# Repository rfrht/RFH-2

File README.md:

# RFH-2
Remote Control unit compatible with most modern Yaesu radios. Includes Schematics, Gerber Files and Board Design.

## What is this?
This is a remote control that is compatible with most modern and recent Yaesu radios. It mimicks the same functionality of [Yaesu FH-2](http://lmgtfy.com/?q=yaesu+fh-2) remote control, at a fraction of the cost ane with a enormous cool factor: YOU CAN ACTUALLY BUILD IT!

Check how [Jim N5JGE](https://www.qrz.com/db/N5JGE) actually built something [**really nifty**](https://github.com/jgedmond/RFH-2/commit/793899766d5572a83a48a860f2a84d2ef02e2b0a) without the need of an enclosure for the board!

## How does the board looks like?
This is the board layout in its full glory (slightly changed from FH-2, because... usability++):

## Did you prototype it?
Yup. Picture below:

## What are the compatible radios?
Yaesu FT-991, FT-991A, FT-950, FTDX-9000, FTDX-5000, FTDX-3000, FT-2000, FTDX-1200, FT-1000MP

## Nice, I liked it! How do I get one?
1. Download the Gerber [.zip file](https://github.com/rfrht/RFH-2/raw/master/Design/RFH-2-gerbers.zip)

2. Send the Gerber ZIP to any PCB Print Service. I have used [JLCPCB](https://jlcpcb.com/quote), they are dead cheap - Paid $2 for 5 boards

3. Buy the switches and the resistors. The most critical part here are the switches: The board has the footprints for this specific switch, which is [Digikey Part EG6117-ND](https://www.digikey.com/products/en?keywords=eg6117-nd). The Resistors and Capacitor are through-hole and the values are in the Schematic.

4. How do I wire it? For wiring, wire the tip of a standard 3-pin audio plug and the `GND` part of the plug. Leave the center floating.

Of course you can also download [Eagle 9](https://www.autodesk.com/products/eagle/free-download) and play with the schematics and PCB layout in [Design](/Design) folder.

## CHANGELOG

### Revision C (May 27, 2024)
* Fixed the flipped Down arrow and F/B button reported in [Issue 1](https://github.com/rfrht/RFH-2/issues/1) by jgedmond - thank you!

### Revision B (Jun 8, 2019)
* Fixed the push-button pinout
* Now makes extensive use of ground plane
* Rewired the board
* Larger holes, suitable for a screw, with symmetrical holes at the board edges
* A through-the-hole pad for the signal input
* Added a few centimeters more to accomodate the $ABOVE changes
* And that's it folks!

### Revision A (Apr 28, 2019)
* Initial release

73s de PY2RAF.

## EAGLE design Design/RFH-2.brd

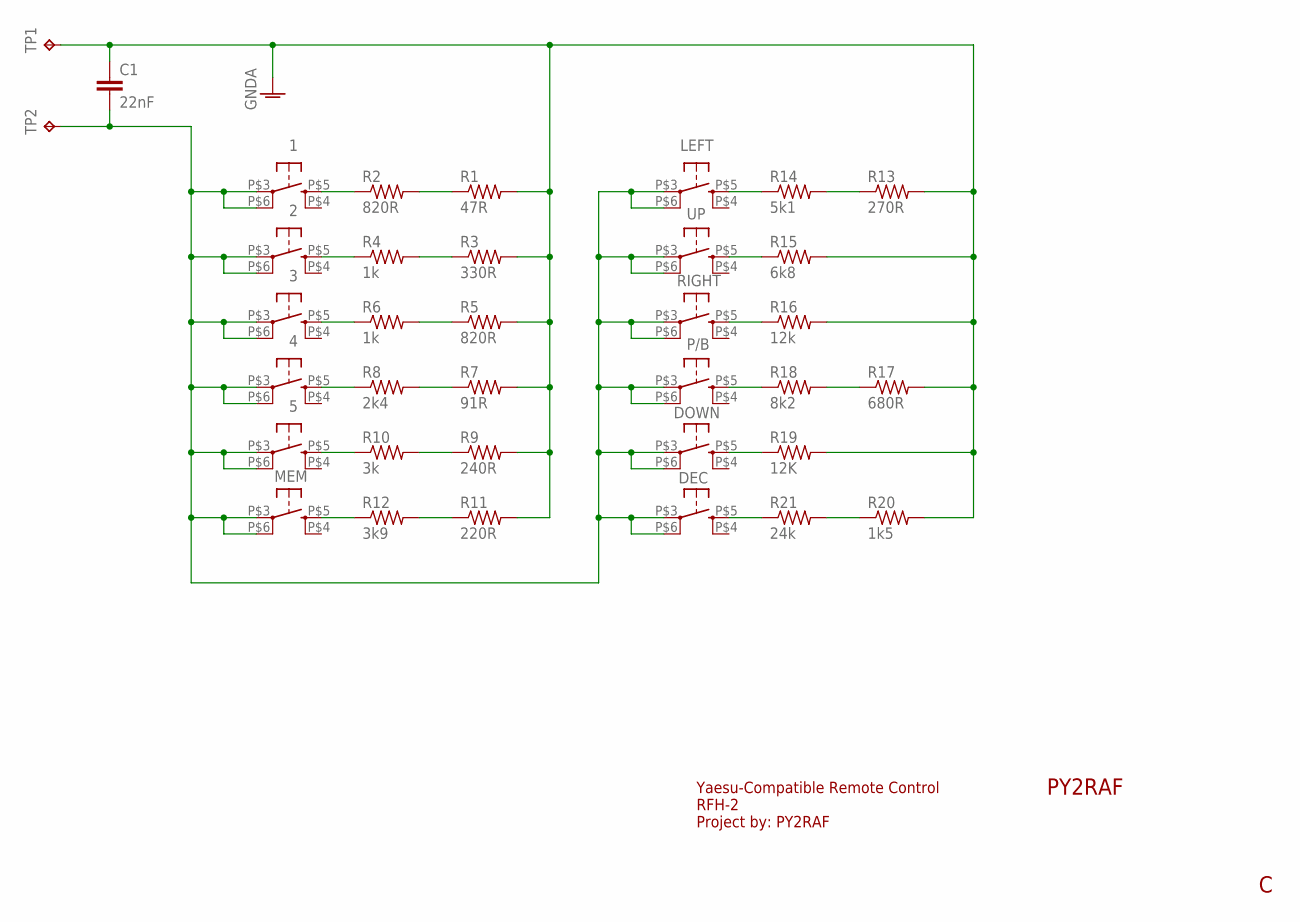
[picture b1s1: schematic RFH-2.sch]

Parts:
1, 2, 3, 4, 5: TL6300-SPST; TL6300
C1: 22nF; C5B3
DEC: TL6300-SPST; TL6300
DOWN: TL6300-SPST; TL6300
LEFT: TL6300-SPST; TL6300
MEM: TL6300-SPST; TL6300
P/B: TL6300-SPST; TL6300
R1: 47R; 0309/10
R2, R5: 820R; 0309/10
R3: 330R; 0309/10
R4, R6: 1k; 0309/10
R7: 91R; 0309/10
R8: 2k4; 0309/10
R9: 240R; 0309/10
R10: 3k; 0309/10
R11: 220R; 0309/10
R12: 3k9; 0309/10
R13: 270R; 0309/10
R14: 5k1; 0309/10
R15: 6k8; 0309/10
R16: 12k; 0309/10
R17: 680R; 0309/10
R18: 8k2; 0309/10
R19: 12K; 0309/10
R20: 1k5; 0309/10
R21: 24k; 0309/10
RIGHT: TL6300-SPST; TL6300
TP1, TP2: TPPAD1-20Y; P1-20Y
UP: TL6300-SPST; TL6300

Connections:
GNDA: C1.1, R1.2, R3.2, R5.2, R7.2, R9.2, R11.2, R13.2, R15.2, R16.2, R17.2, R19.2, R20.2, TP1.TP
unnamed: 1.P$3, 1.P$6 (P1), 2.P$3, 2.P$6 (P1), 3.P$3, 3.P$6 (P1), 4.P$3, 4.P$6 (P1), 5.P$3, 5.P$6 (P1), C1.2, DEC.P$3, DEC.P$6 (P1), DOWN.P$3, DOWN.P$6 (P1), LEFT.P$3, LEFT.P$6 (P1), MEM.P$3, MEM.P$6 (P1), P/B.P$3, P/B.P$6 (P1), RIGHT.P$3, RIGHT.P$6 (P1), TP2.TP, UP.P$3, UP.P$6 (P1)
unnamed: R17.1, R18.2
unnamed: LEFT.P$5 (S), R14.1
unnamed: R15.1, UP.P$5 (S)
unnamed: R16.1, RIGHT.P$5 (S)
unnamed: P/B.P$5 (S), R18.1
unnamed: DOWN.P$5 (S), R19.1
unnamed: 1.P$5 (S), R2.1
unnamed: DEC.P$5 (S), R21.1
unnamed: 2.P$5 (S), R4.1
unnamed: 3.P$5 (S), R6.1
unnamed: 4.P$5 (S), R8.1
unnamed: 5.P$5 (S), R10.1
unnamed: MEM.P$5 (S), R12.1
unnamed: R13.1, R14.2
unnamed: R1.1, R2.2
unnamed: R3.1, R4.2
unnamed: R5.1, R6.2
unnamed: R7.1, R8.2
unnamed: R9.1, R10.2
unnamed: R11.1, R12.2
unnamed: R20.1, R21.2

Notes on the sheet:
Yaesu-Compatible Remote Control RFH-2 Project by: PY2RAF
PY2RAF

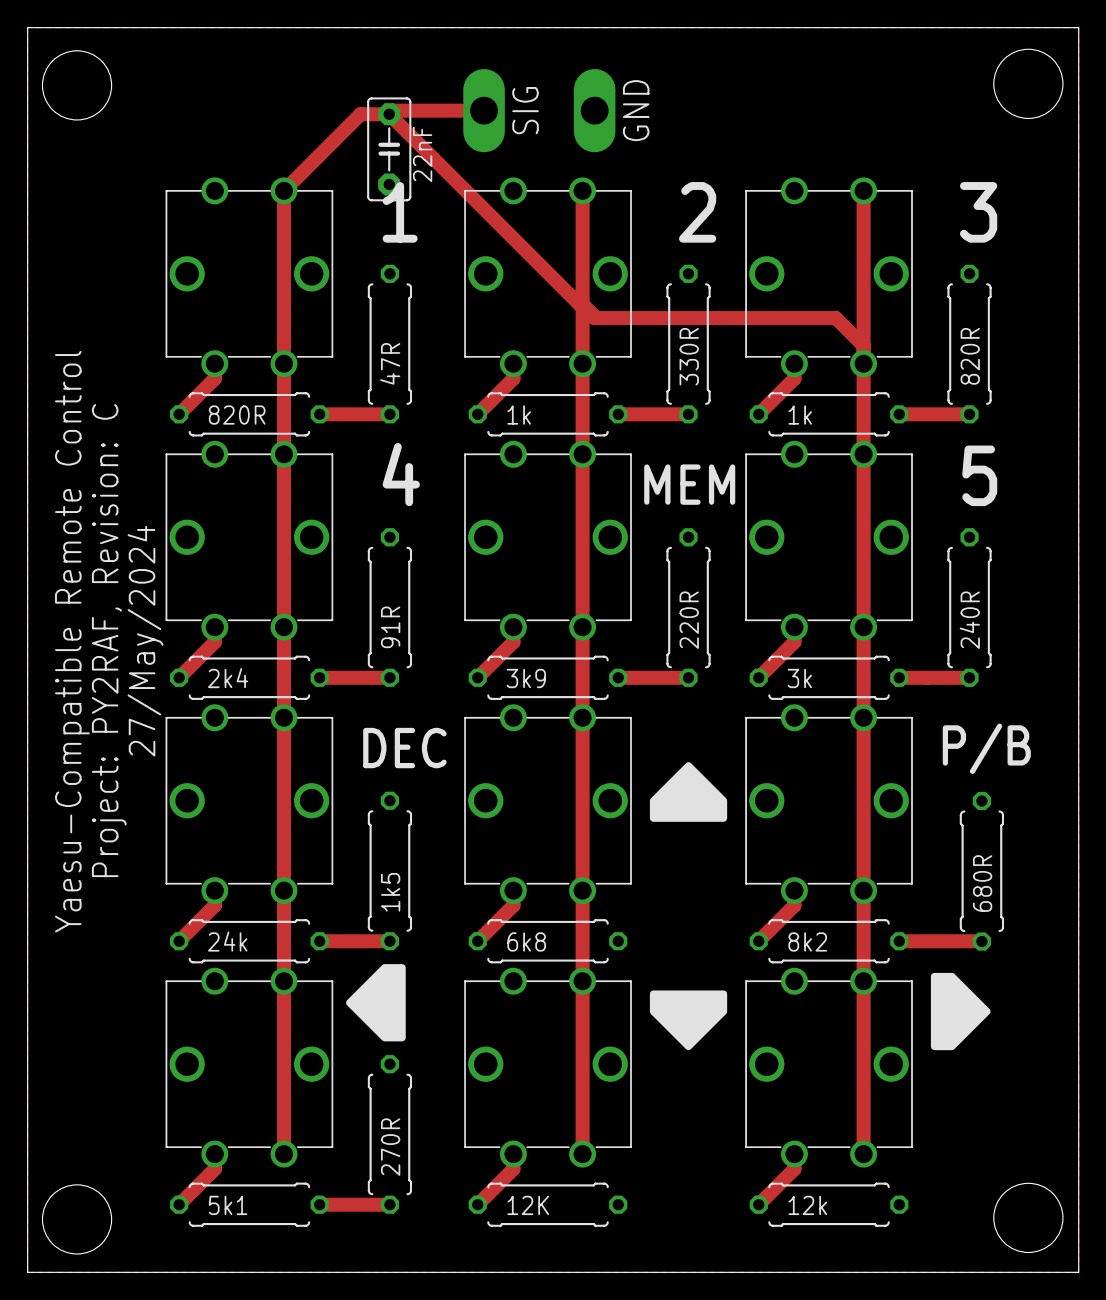
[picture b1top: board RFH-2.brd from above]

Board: 2 copper layers, 76.0 x 90.0 mm, 36 parts (0 on the bottom side), 23 nets.

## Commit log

2019-04-28 Initial commit: Revision A
2019-04-28 Images rescaled
2019-04-28 Added Prototype picture
2019-04-28 Added Prototype to Readme
2019-04-28 Readme Quickie
2019-04-29 Added notice about different layout
2019-04-30 Added model compatibility
2019-04-30 Moar Updated Readme
2019-06-09 Revision B
    * Fixed the push-button pinout
    * Now makes extensive use of ground plane
    * Rewired the board
    * Larger holes, suitable for a screw, with symmetrical holes at the
    * board edges
    * A through-the-hole pad for the signal input
2024-05-27 Schematic: Fixes #1
    https://github.com/jgedmond pointed a flipped Down Arrow and F/B
    button. Thanks for reporting it!
2024-05-27 Board: Fixed silkscreen missing component values
2024-06-05 Added reference to Jim's board
